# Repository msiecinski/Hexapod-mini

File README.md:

# Hexapod mini
 tiny hexapod robot

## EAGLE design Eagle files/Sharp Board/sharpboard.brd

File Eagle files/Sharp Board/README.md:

# List of elements at sharp board
- 1 x Sharp sensor GP2Y0D340K 
- 1 x Resistor 1 ohm
- 1 x Capacitor 0,1uF

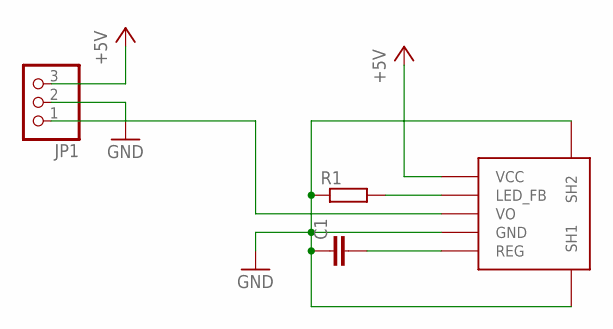
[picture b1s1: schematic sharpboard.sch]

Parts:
C1: C-EUC0805; C0805
JP1: PINHD-1X3; 1X03
R1: R-EU_R0805; R0805
U$2: GP2Y0D340K0F

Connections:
+5V: JP1.3, U$2.P$1 (VCC)
GND: C1.1, JP1.2, R1.1, U$2.P$4 (GND), U$2.P$6 (SH1), U$2.P$7 (SH2)
unnamed: R1.2, U$2.P$2 (LED_FB)
unnamed: C1.2, U$2.P$5 (REG)
unnamed: JP1.1, U$2.P$3 (VO)

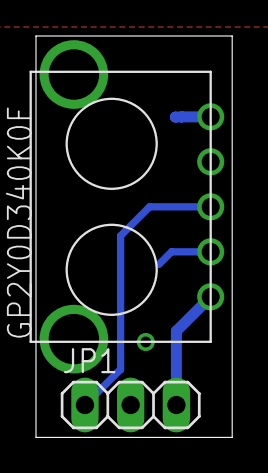
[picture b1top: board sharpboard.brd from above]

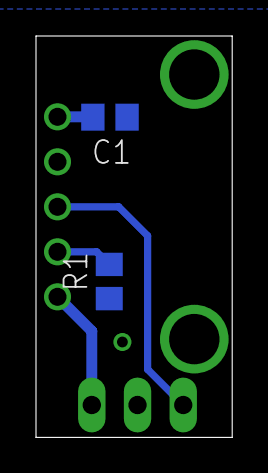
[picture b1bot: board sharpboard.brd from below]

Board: 2 copper layers, 10.9 x 22.3 mm, 4 parts (2 on the bottom side), 5 nets.

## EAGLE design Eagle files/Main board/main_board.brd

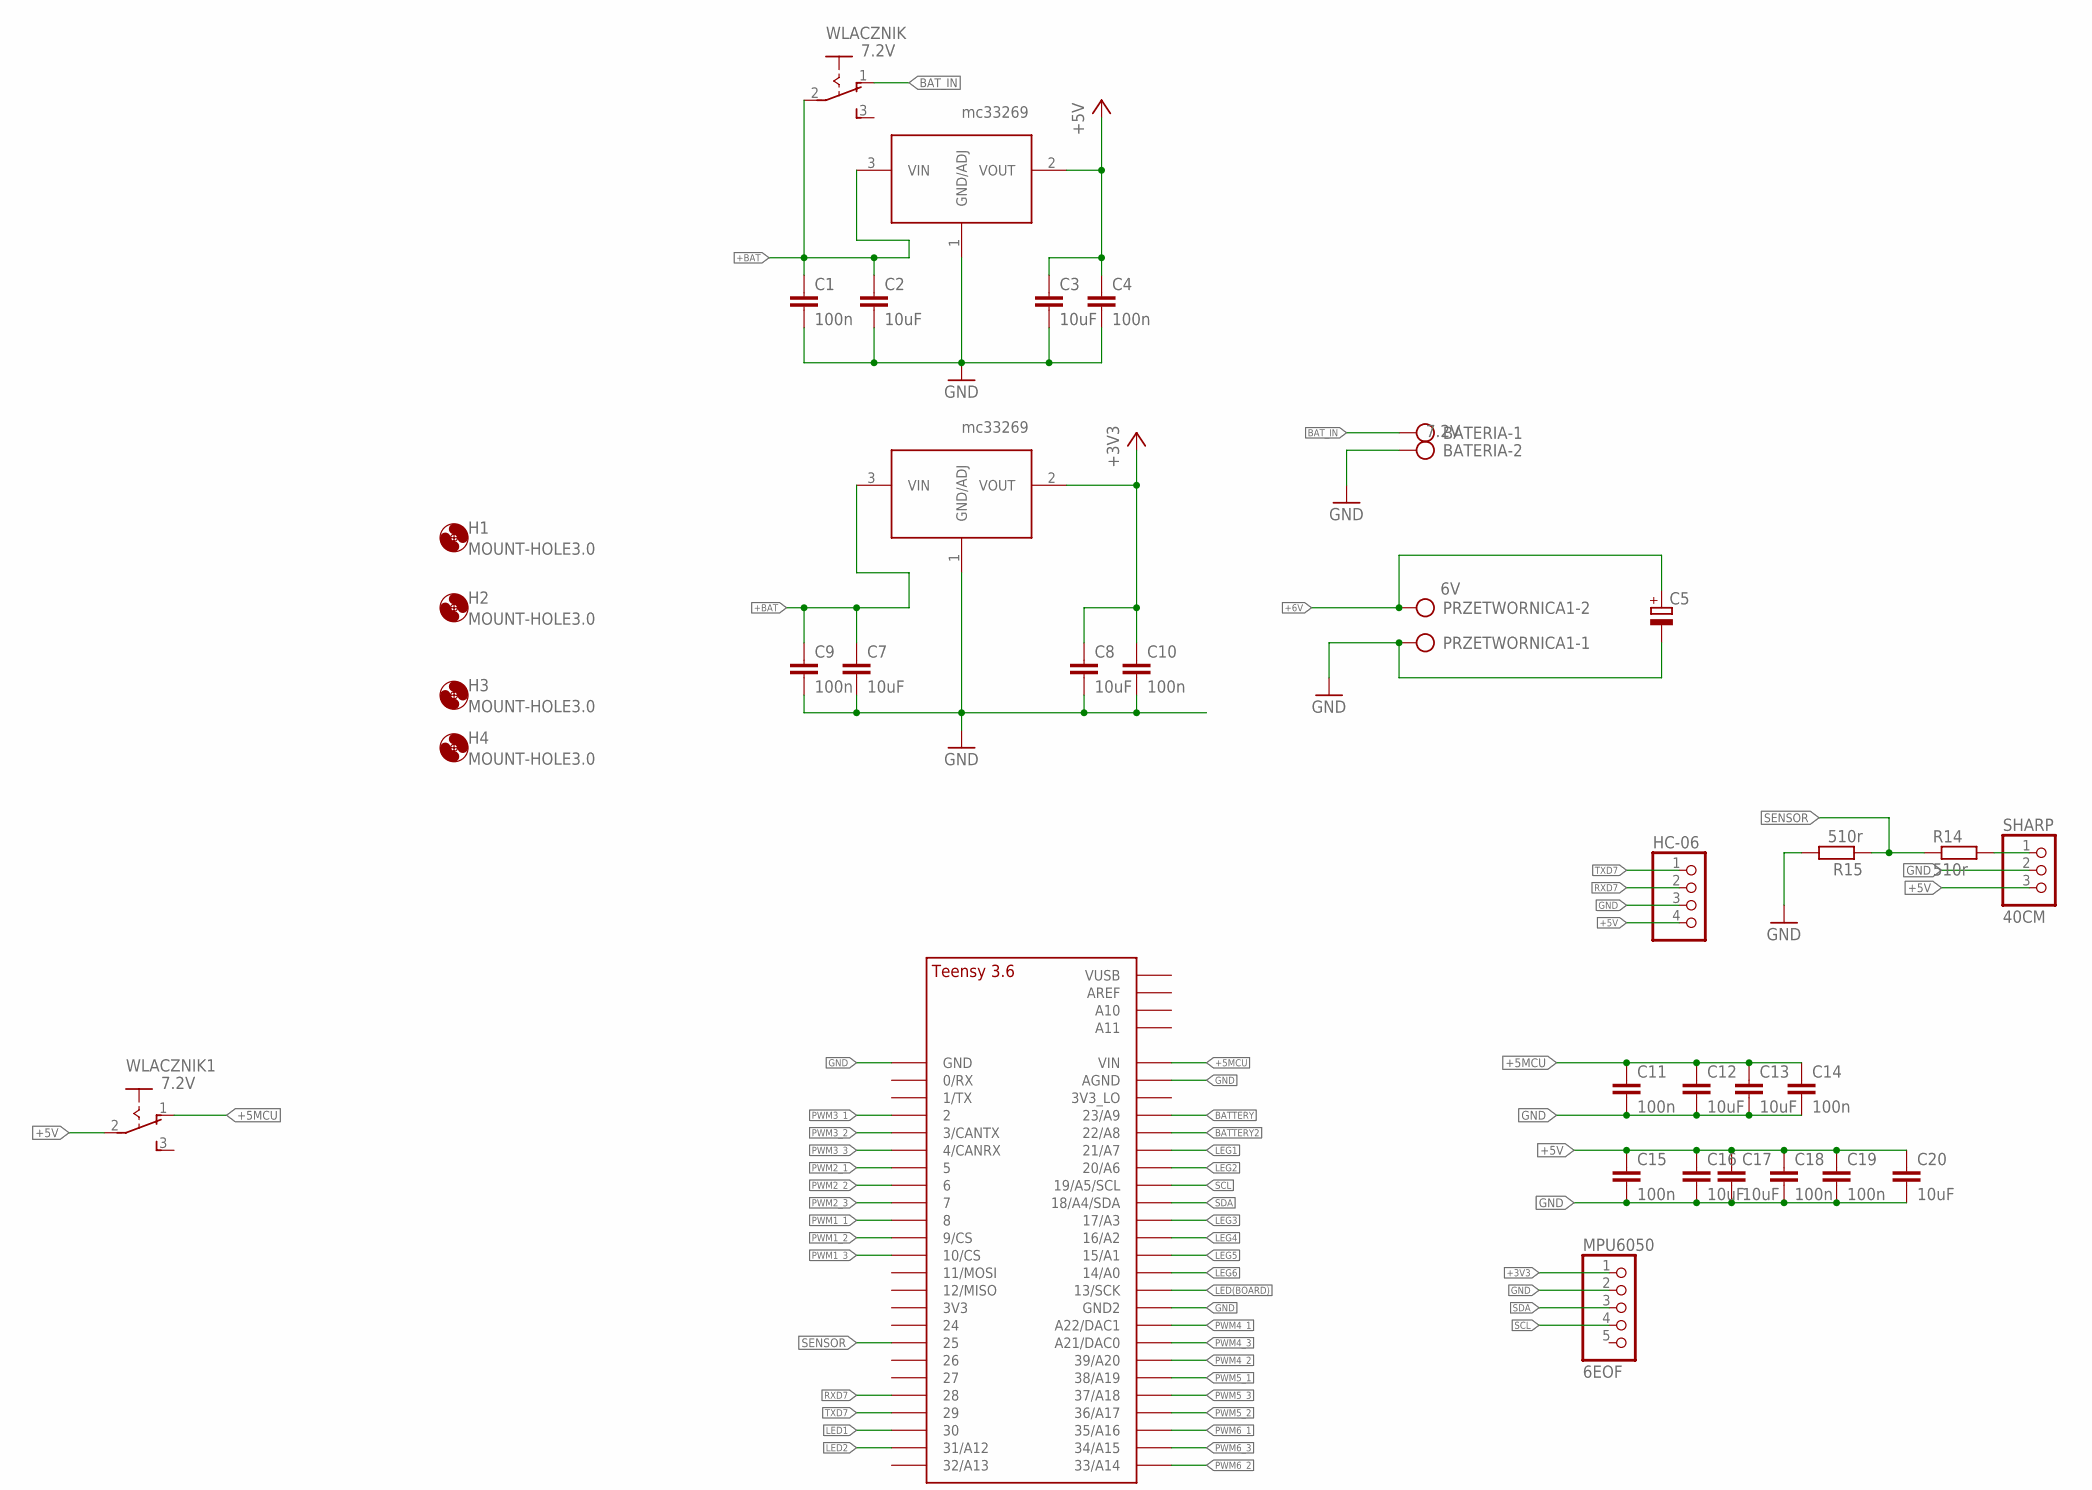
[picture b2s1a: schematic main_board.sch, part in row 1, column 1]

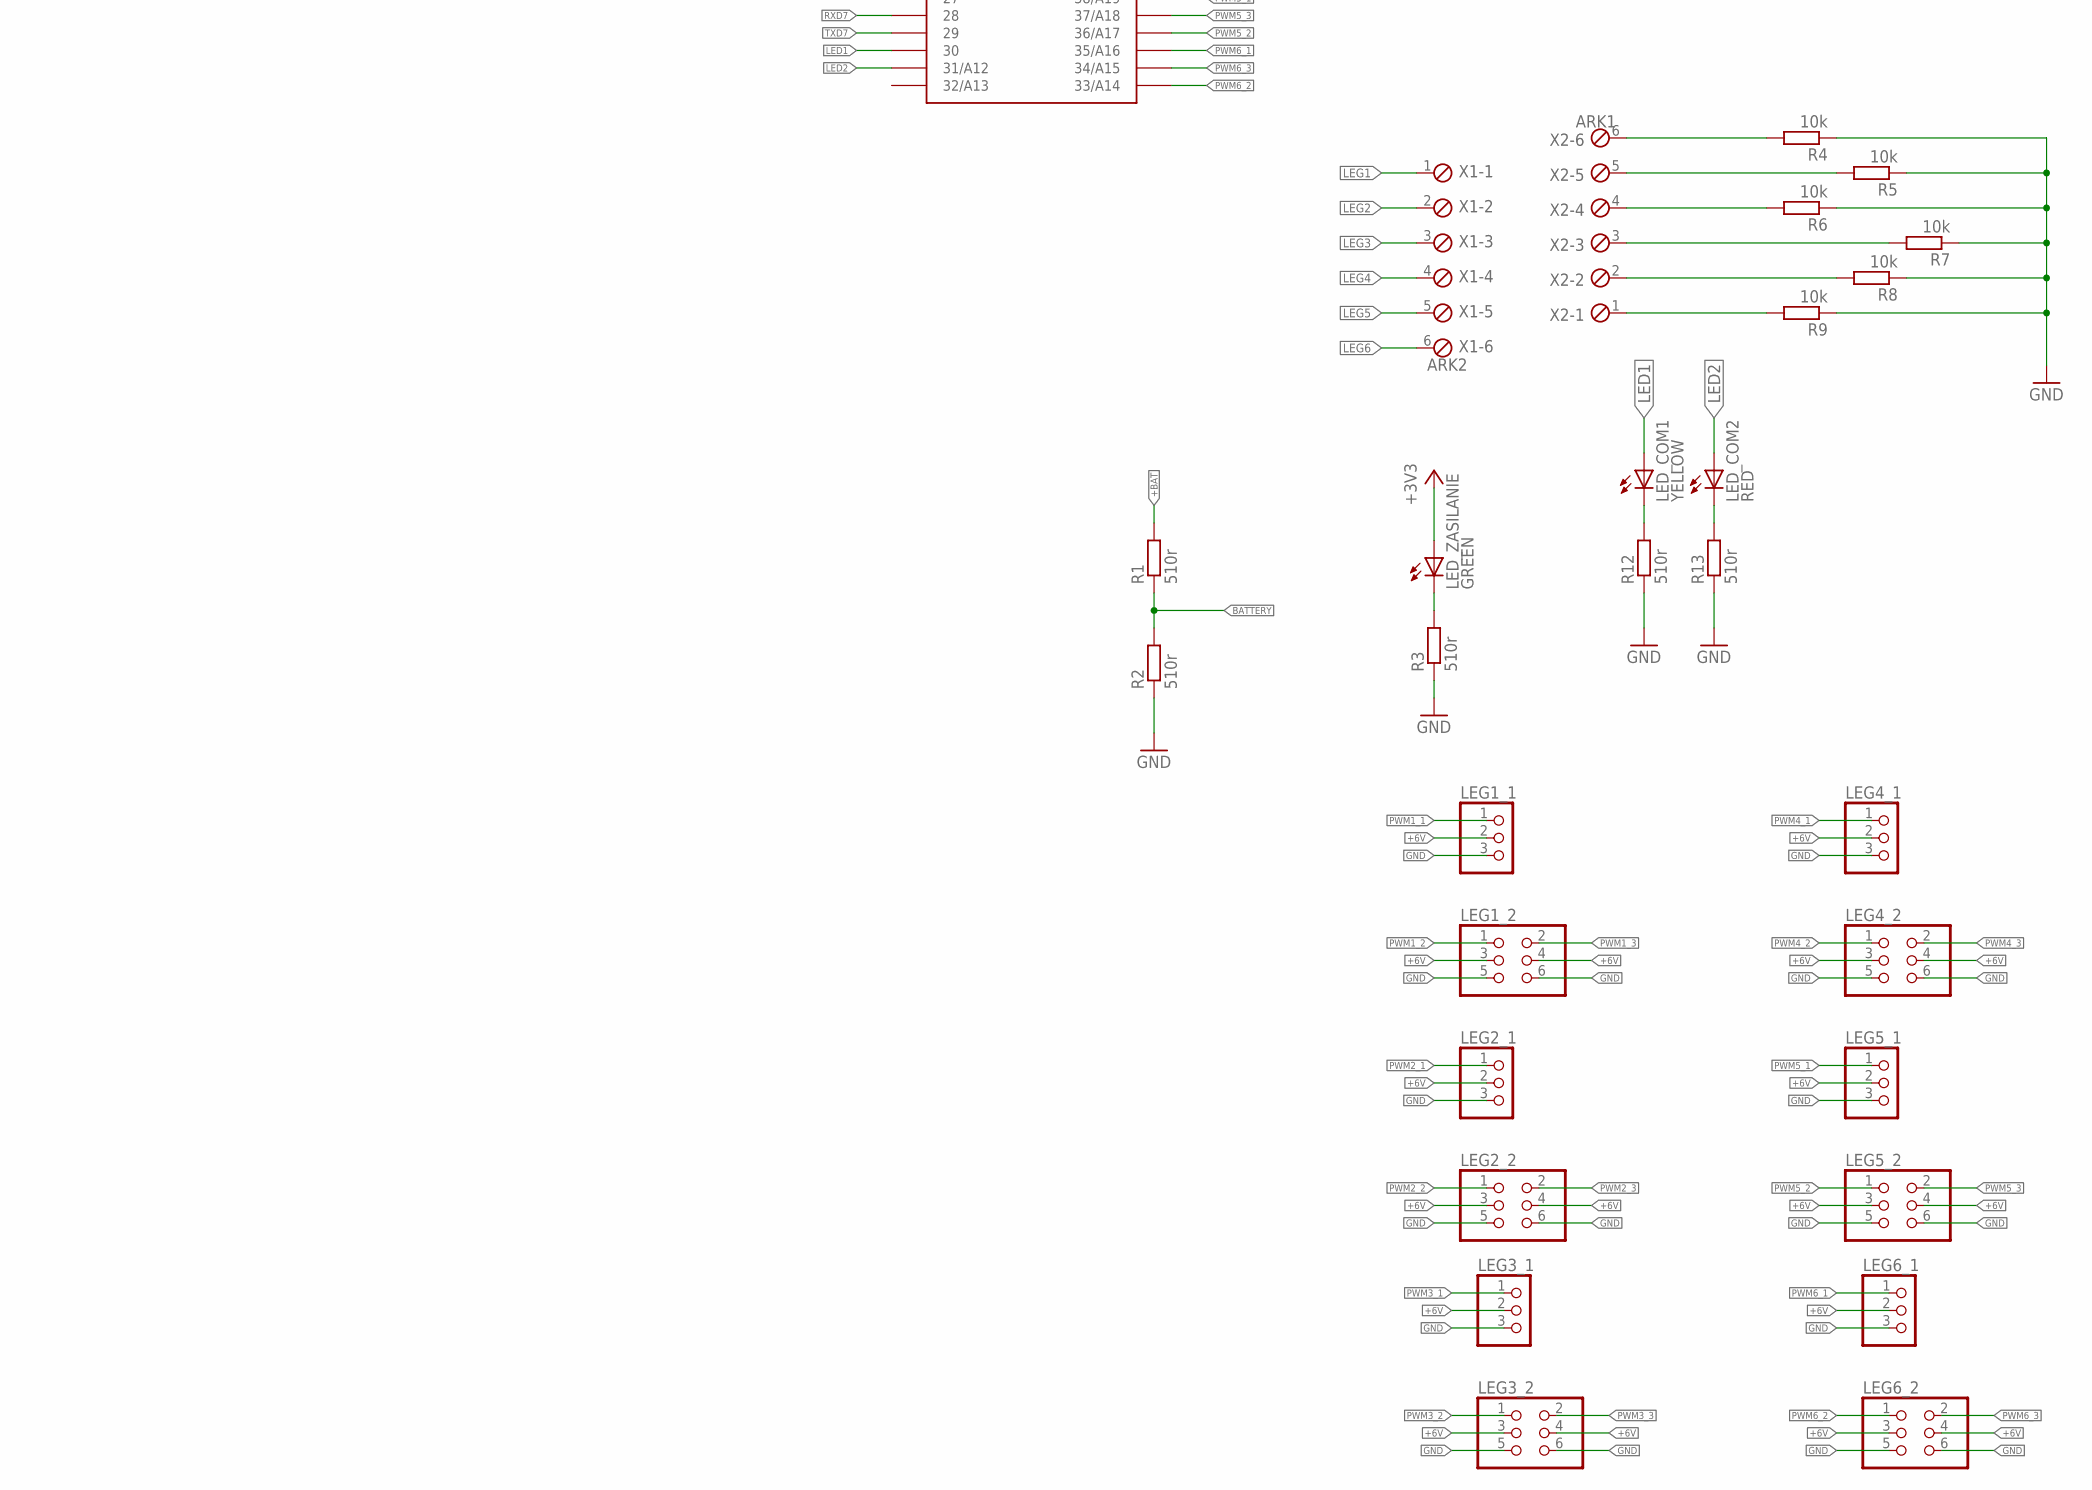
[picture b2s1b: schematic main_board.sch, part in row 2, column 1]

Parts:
3V, 5V: MC33269; TO220
BATERIA: 7.2V; AK300/2
C1, C4, C9, C10, C11, C14, C15, C18, C19: 100n; C0805
C2, C3, C7, C8, C12, C13, C16, C17, C20: 10uF; C1206
C5: CPOL-EU150CLZ-1014; 150CLZ-1014
H1, H2, H3, H4: MOUNT-HOLE3.0; 3,0
HC-06: PINHD-1X4; 1X04
LED_COM1: YELLOW; SML0805
LED_COM2: RED; SML0805
LED_ZASILANIE: GREEN; SML0805
LEG1_1, LEG2_1, LEG3_1, LEG4_1, LEG5_1, LEG6_1: PINHD-1X3; 1X03
LEG1_2, LEG2_2, LEG3_2, LEG4_2, LEG5_2, LEG6_2: PINHD-2X3; 2X03
MPU6050: 6EOF; 1X05
PRZETWORNICA1: 6V; AK300/2
R1, R2, R3, R12, R13, R14, R15: 510r; R0805
R4, R5, R6, R7, R8, R9: 10k; R0805
SHARP: 40CM; 1X03
TEENSY41: TEENSY_3.5/3.6_BASIC
WLACZNIK, WLACZNIK1: 7.2V; 255SB
X1: ARK2; 6POL254
X2: ARK1; 6POL254

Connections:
+3V3: 3V.2 (VOUT), C8.1, C10.1, LED_ZASILANIE.A, MPU6050.1
+5MCU: C11.1, C12.1, C13.1, C14.1, TEENSY41.VIN, WLACZNIK1.1 (O)
+5V: 5V.2 (VOUT), C3.1, C4.1, C15.1, C16.1, C17.1, C18.1, C19.1, C20.1, HC-06.4, SHARP.3, WLACZNIK1.2
+6V: C5.+, LEG1_1.2, LEG1_2.3, LEG1_2.4, LEG2_1.2, LEG2_2.3, LEG2_2.4, LEG3_1.2, LEG3_2.3, LEG3_2.4, LEG4_1.2, LEG4_2.3, LEG4_2.4, LEG5_1.2, LEG5_2.3, LEG5_2.4, LEG6_1.2, LEG6_2.3, LEG6_2.4, PRZETWORNICA1.2
+BAT: 3V.3 (VIN), 5V.3 (VIN), C1.1, C2.1, C7.1, C9.1, R1.2, WLACZNIK.2
BATTERY: R1.1, R2.2, TEENSY41.23/A9
BAT_IN: BATERIA.1, WLACZNIK.1 (O)
EN_PRZETWOTNICA: TEENSY41.12/MISO; also elsewhere on the board
GND: 3V.1 (GND/ADJ), 5V.1 (GND/ADJ), BATERIA.2, C1.2, C2.2, C3.2, C4.2, C5.-, C7.2, C8.2, C9.2, C10.2, C11.2, C12.2, C13.2, C14.2, C15.2, C16.2, C17.2, C18.2, C19.2, C20.2, HC-06.3, LEG1_1.3, LEG1_2.5, LEG1_2.6, LEG2_1.3, LEG2_2.5, LEG2_2.6, LEG3_1.3, LEG3_2.5, LEG3_2.6, LEG4_1.3, LEG4_2.5, LEG4_2.6, LEG5_1.3, LEG5_2.5, LEG5_2.6, LEG6_1.3, LEG6_2.5, LEG6_2.6, MPU6050.2, PRZETWORNICA1.1, R2.1, R3.1, R4.1, R5.1, R6.1, R7.1, R8.1, R9.1, R12.1, R13.1, R15.2, SHARP.2, TEENSY41.AGND, TEENSY41.GND, TEENSY41.GND2; also elsewhere on the board
LED1: LED_COM1.A, TEENSY41.30
LED2: LED_COM2.A, TEENSY41.31/A12
LEG1: TEENSY41.21/A7, X1.1
LEG2: TEENSY41.20/A6, X1.2
LEG3: TEENSY41.17/A3, X1.3
LEG4: TEENSY41.16/A2, X1.4
LEG5: TEENSY41.15/A1, X1.5
LEG6: TEENSY41.14/A0, X1.6
unnamed: R4.2, X2.6
unnamed: R5.2, X2.5
unnamed: R6.2, X2.4
unnamed: LED_ZASILANIE.C, R3.2
unnamed: R7.2, X2.3
unnamed: R8.2, X2.2
unnamed: R9.2, X2.1
unnamed: LED_COM1.C, R12.2
unnamed: LED_COM2.C, R13.2
unnamed: R14.2, SHARP.1
PWM1_1: LEG1_1.1, TEENSY41.8
PWM1_2: LEG1_2.1, TEENSY41.9/CS
PWM1_3: LEG1_2.2, TEENSY41.10/CS
PWM2_1: LEG2_1.1, TEENSY41.5
PWM2_2: LEG2_2.1, TEENSY41.6
PWM2_3: LEG2_2.2, TEENSY41.7
PWM3_1: LEG3_1.1, TEENSY41.2
PWM3_2: LEG3_2.1, TEENSY41.3/CANTX
PWM3_3: LEG3_2.2, TEENSY41.4/CANRX
PWM4_1: LEG4_1.1, TEENSY41.A22/DAC1
PWM4_2: LEG4_2.1, TEENSY41.39/A20
PWM4_3: LEG4_2.2, TEENSY41.21/DAC0 (A21/DAC0)
PWM5_1: LEG5_1.1, TEENSY41.38/A19
PWM5_2: LEG5_2.1, TEENSY41.36/A17
PWM5_3: LEG5_2.2, TEENSY41.37/A18
PWM6_1: LEG6_1.1, TEENSY41.35/A16
PWM6_2: LEG6_2.1, TEENSY41.33/A14
PWM6_3: LEG6_2.2, TEENSY41.34/A15
RXD7: HC-06.2, TEENSY41.28
SCL: MPU6050.4, TEENSY41.19/A5/SCL
SDA: MPU6050.3, TEENSY41.18/A4/SDA
SENSOR: R14.1, R15.1, TEENSY41.25
TXD7: HC-06.1, TEENSY41.29

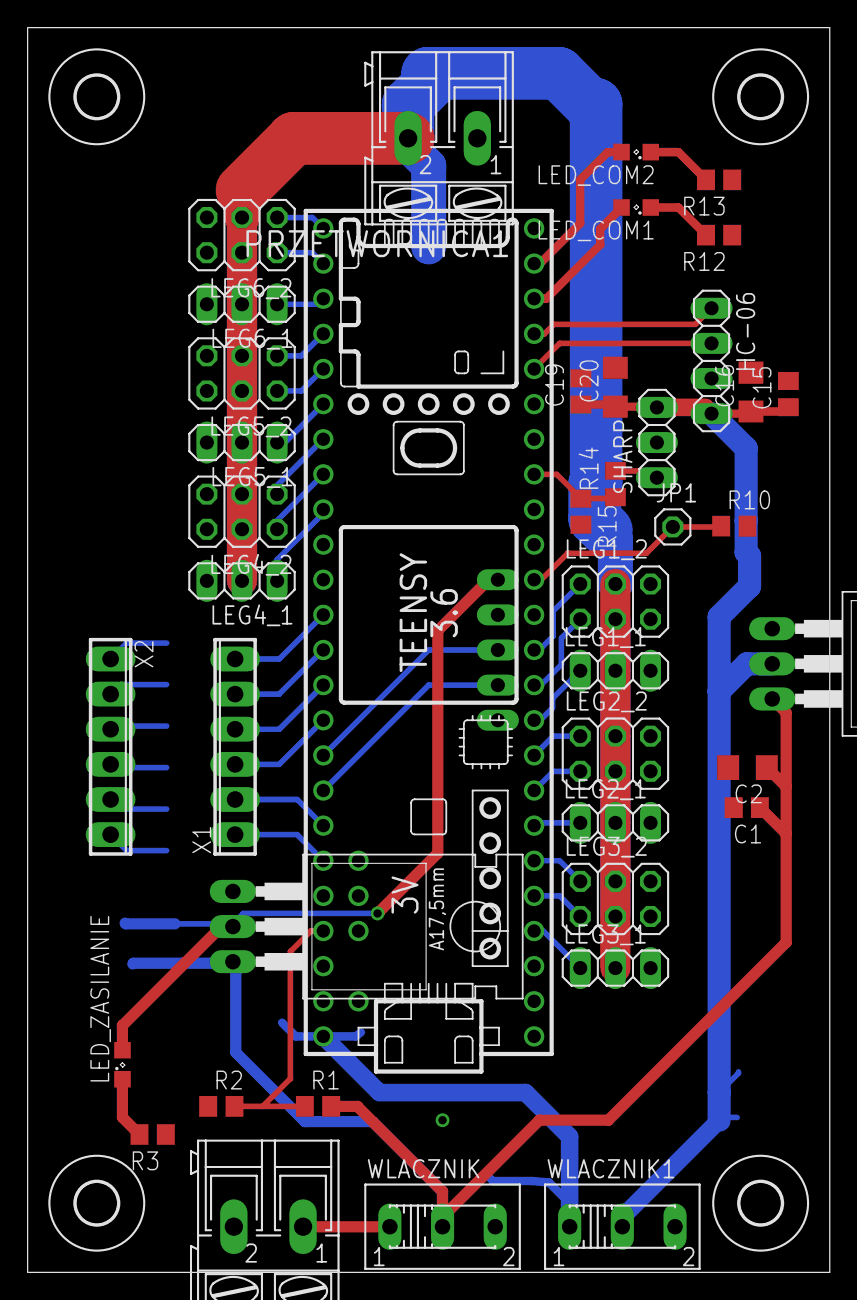
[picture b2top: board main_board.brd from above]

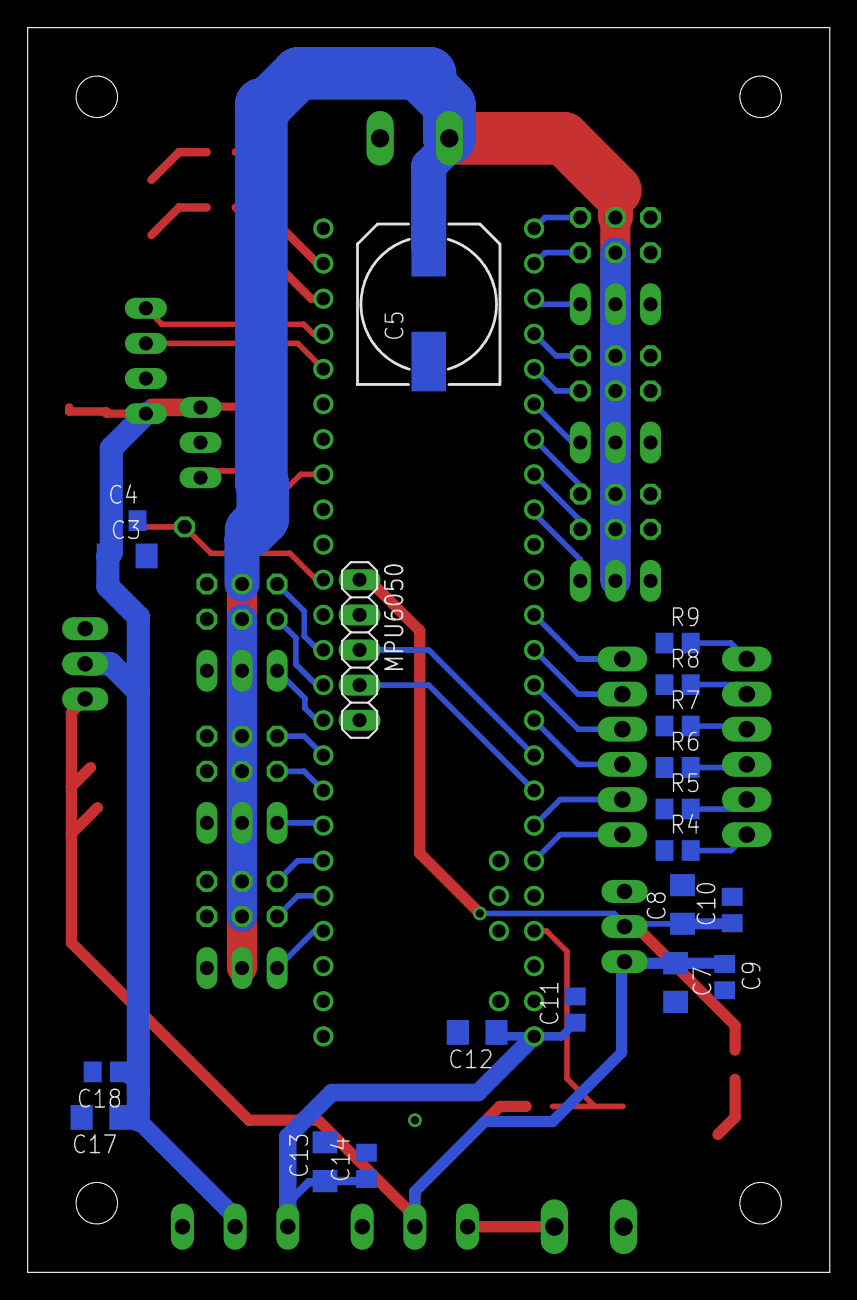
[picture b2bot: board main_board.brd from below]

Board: 2 copper layers, 58.0 x 90.0 mm, 65 parts (20 on the bottom side), 50 nets.

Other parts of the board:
JP1: 1X01
R10: 100k; R0805

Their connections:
EN_PRZETWOTNICA: JP1.1, R10.1; also elsewhere on the board
GND: R10.2; also elsewhere on the board

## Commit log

2022-08-19 Eagle files
    First test version pcb board
2022-08-19 update pcb file
    change eagle file name
2022-08-19 update pcb
    -increase servo power line width
    -added step-down regulator enable
2022-08-19 Update main_board.brd
    Deacrease board size
2022-08-29 Update main_board.brd
    Move MPU position
2022-08-29 Update main_board.sch
    Fix servo power connection
2022-08-29 Fix connection between servo power line
2022-08-29 Fix sch file
2022-08-30 Added sharp sensor PCB board and schematic
    Board with distance measuring sensor(GP2Y0D340K)
2023-10-21 Added source code(vsc)
    Added source code project in visual studio code
    -first, not tested yet implementation servos control
2023-10-22 Fix serwo lib
    -added pin mode setup
    -fix interrupt counter
    -update calibration value
2023-10-22 Update Robot lib
    -fix reference initialization;
    -added api for angle setup;
2023-10-22 Serwo lib
    - update typing and includes
2023-10-22 Added kinematics lib
2023-10-22 Added new constans
2023-10-22 Update Robot.cpp
    -added kinematics lib
    -added deg/rad typing during constructing object and as const value;
2023-10-22 Update Kinematics.hpp
    Change to signed type for position
2023-10-22 update
    -Added set position function
    -Added constant array with joints
2023-10-23 Update serwo lib
    Added parameters for lib, now can easily change
    -signal resolution,
    -serwo position ranges
    -duty pwm ranges
2023-10-23 update serwo lib
    -change attach function, for be "more uniwersal" by template and initializer list
2023-10-23 delete eagle files
    delete files
2023-10-26 Added mcu frequency modyfication
2023-10-29 Added delay lib
    -lib for invoke attached functions;
2023-10-29 update
    -added blikLed function
2023-10-29 Update Robot.cpp
    Update blink function
2023-10-30 Added MPU6050 lib
2023-10-30 Some changes
    -added MPU6050 object;
    -changed Delay object reference and Serwo object reference into "normal" objects;
2023-11-11 Change container type
    Change buff type from std::vector to std::map
2023-11-12 minor changes
2023-11-12 minnor changes
2024-04-29 synch
2024-05-29 Fix names
2024-07-23 Updates for easier debug
    added _debug_ definition for easier debug class private member(tempolary set as public ifdef _debug_
    added some description in serwo lib;
2024-07-23 Update .gitignore
    mac file
